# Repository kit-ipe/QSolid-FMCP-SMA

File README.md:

# FMC+ SMA

## Cloning the repository
- Libraries used in the project are in this other [cern repository](https://gitlab.cern.ch/p2-xware/hardware/kicad-pcbs/kit-kicad-library) or [kit repository](https://git.scc.kit.edu/cms-tt/hardware/kicad-pcbs/kit-kicad-library) and need to be linked using an **Environment Variable** inside KiCad (Preferences -> Configure Paths... ->) right after opening the project
 
  `KICAD_USER_LIBRARY = /path/to/KIT_KiCad_Library`

## 3D Views

### Top

### Bottom

## LICENSE

Copyright Luis Ardila, Marvin Fuchs, Robert Gartmann, Lukas Scheller 2023.

This source describes Open Hardware and is licensed under the CERN-OHL-P v2
You may redistribute and modify this documentation and make products
using it under the terms of the CERN-OHL-P v2 [https:/cern.ch/cern-ohl](https:/cern.ch/cern-ohl).
This documentation is distributed WITHOUT ANY EXPRESS OR IMPLIED
WARRANTY, INCLUDING OF MERCHANTABILITY, SATISFACTORY QUALITY
AND FITNESS FOR A PARTICULAR PURPOSE. Please see the CERN-OHL-P v2
for applicable conditions.

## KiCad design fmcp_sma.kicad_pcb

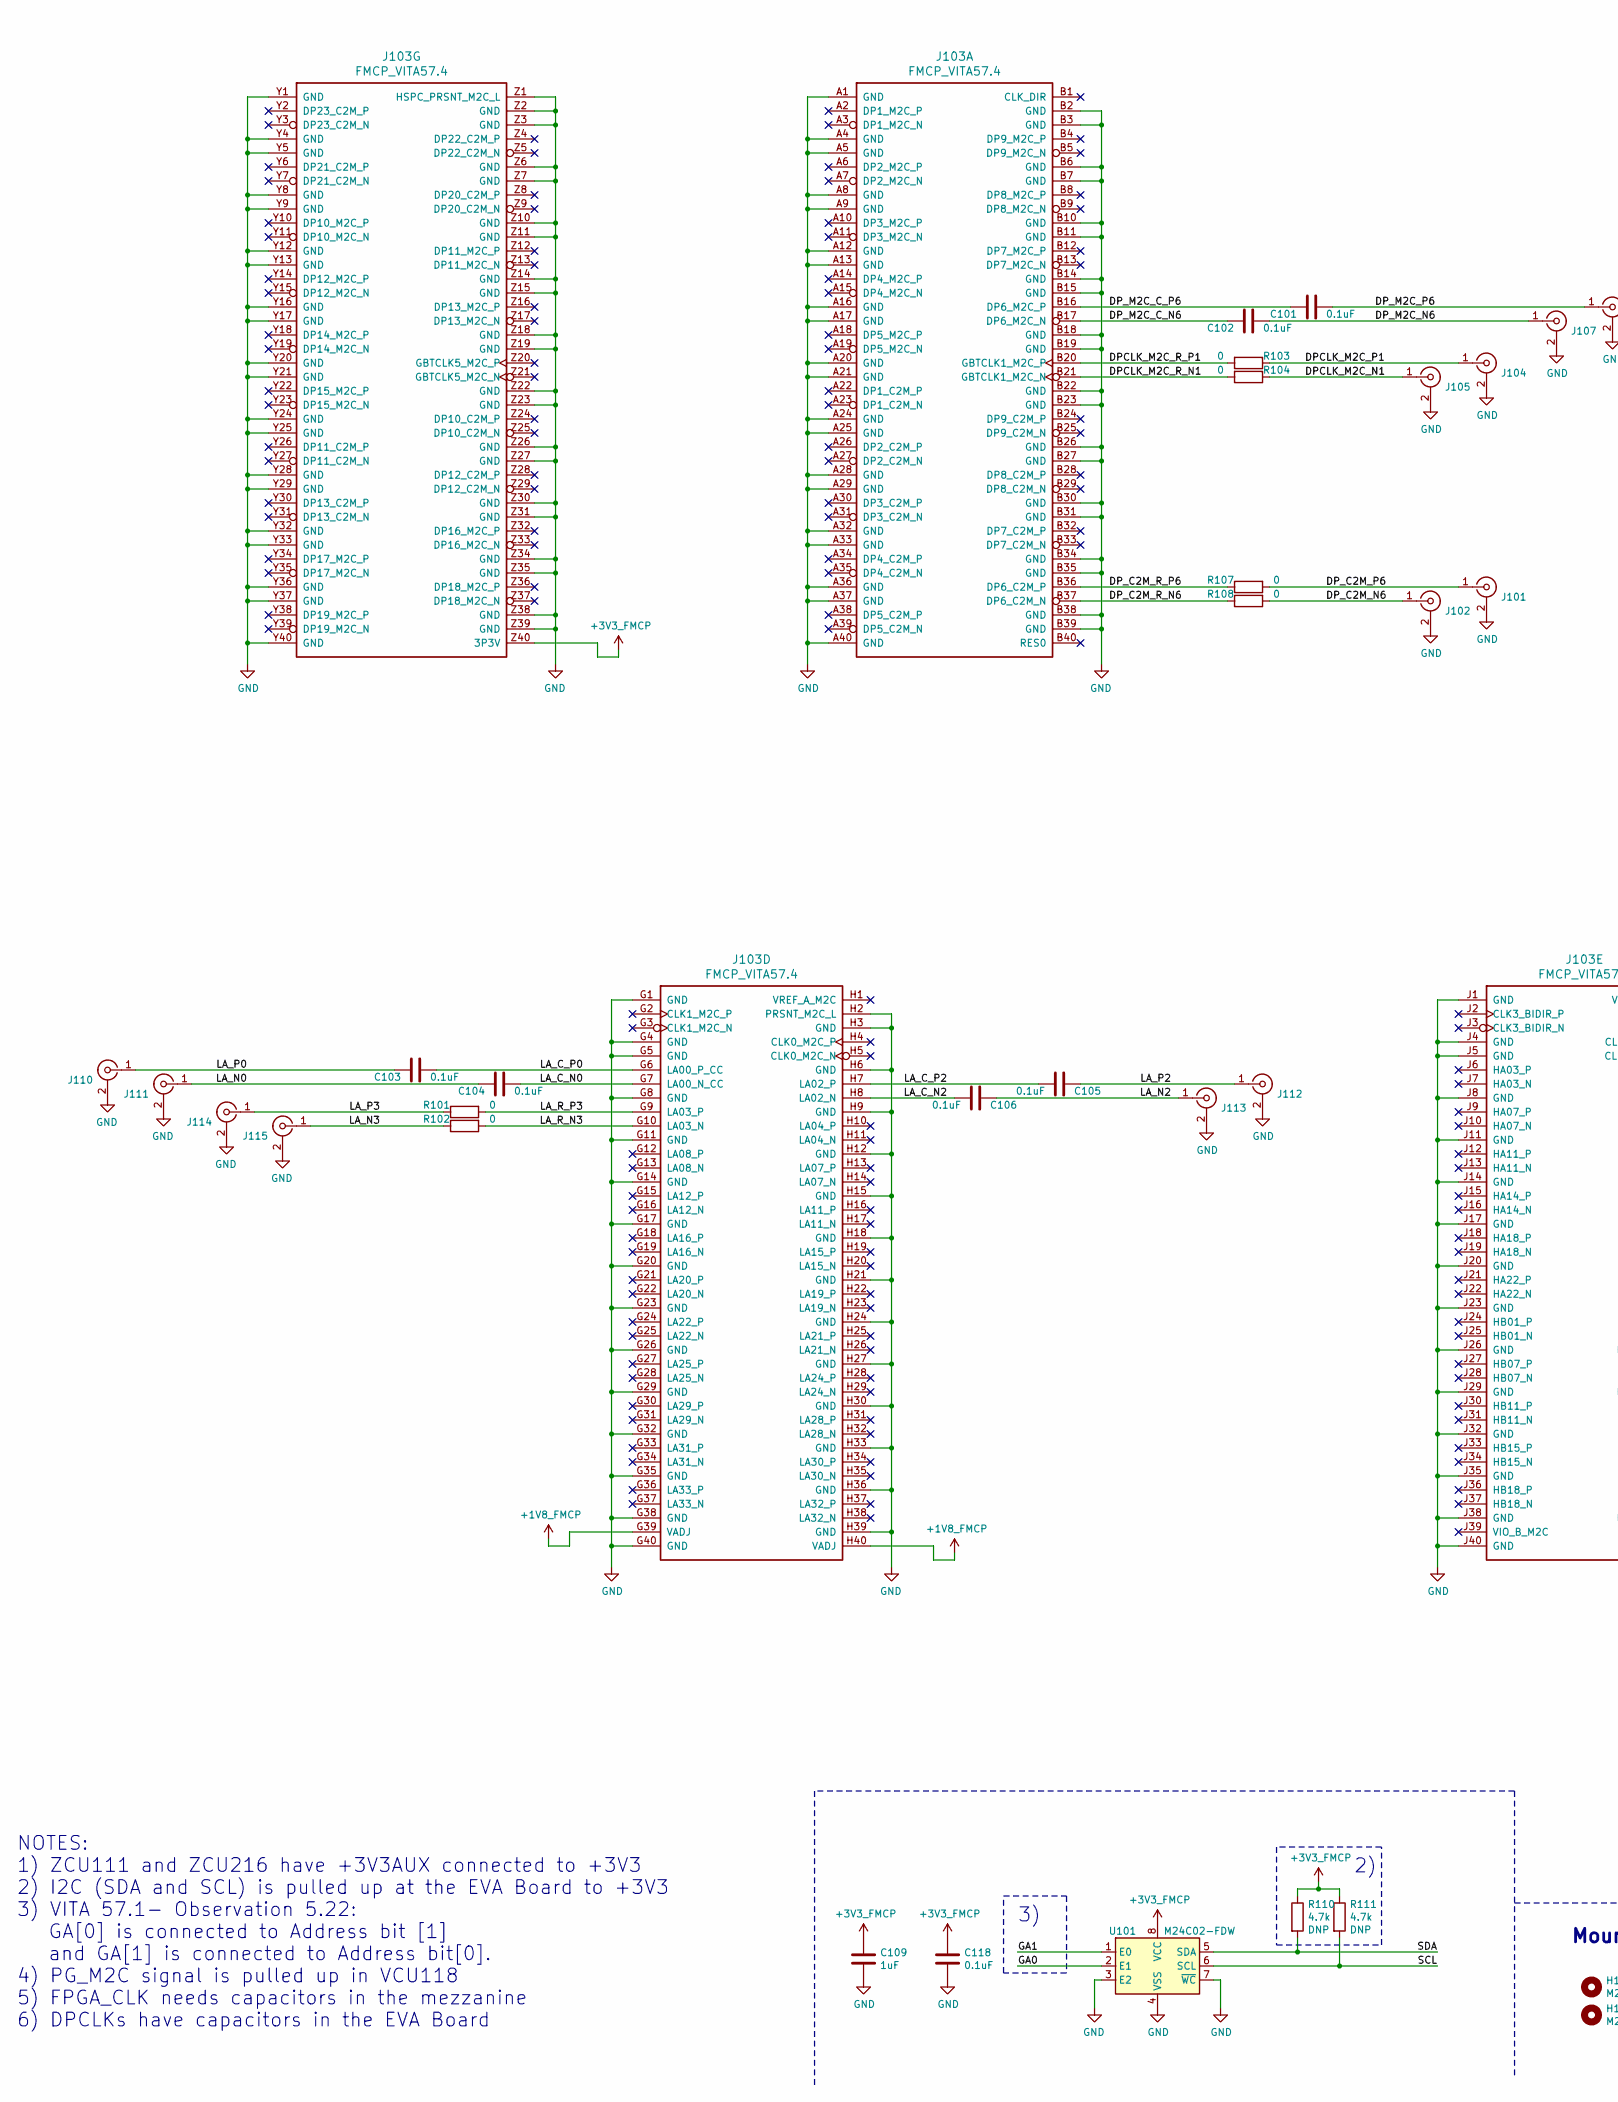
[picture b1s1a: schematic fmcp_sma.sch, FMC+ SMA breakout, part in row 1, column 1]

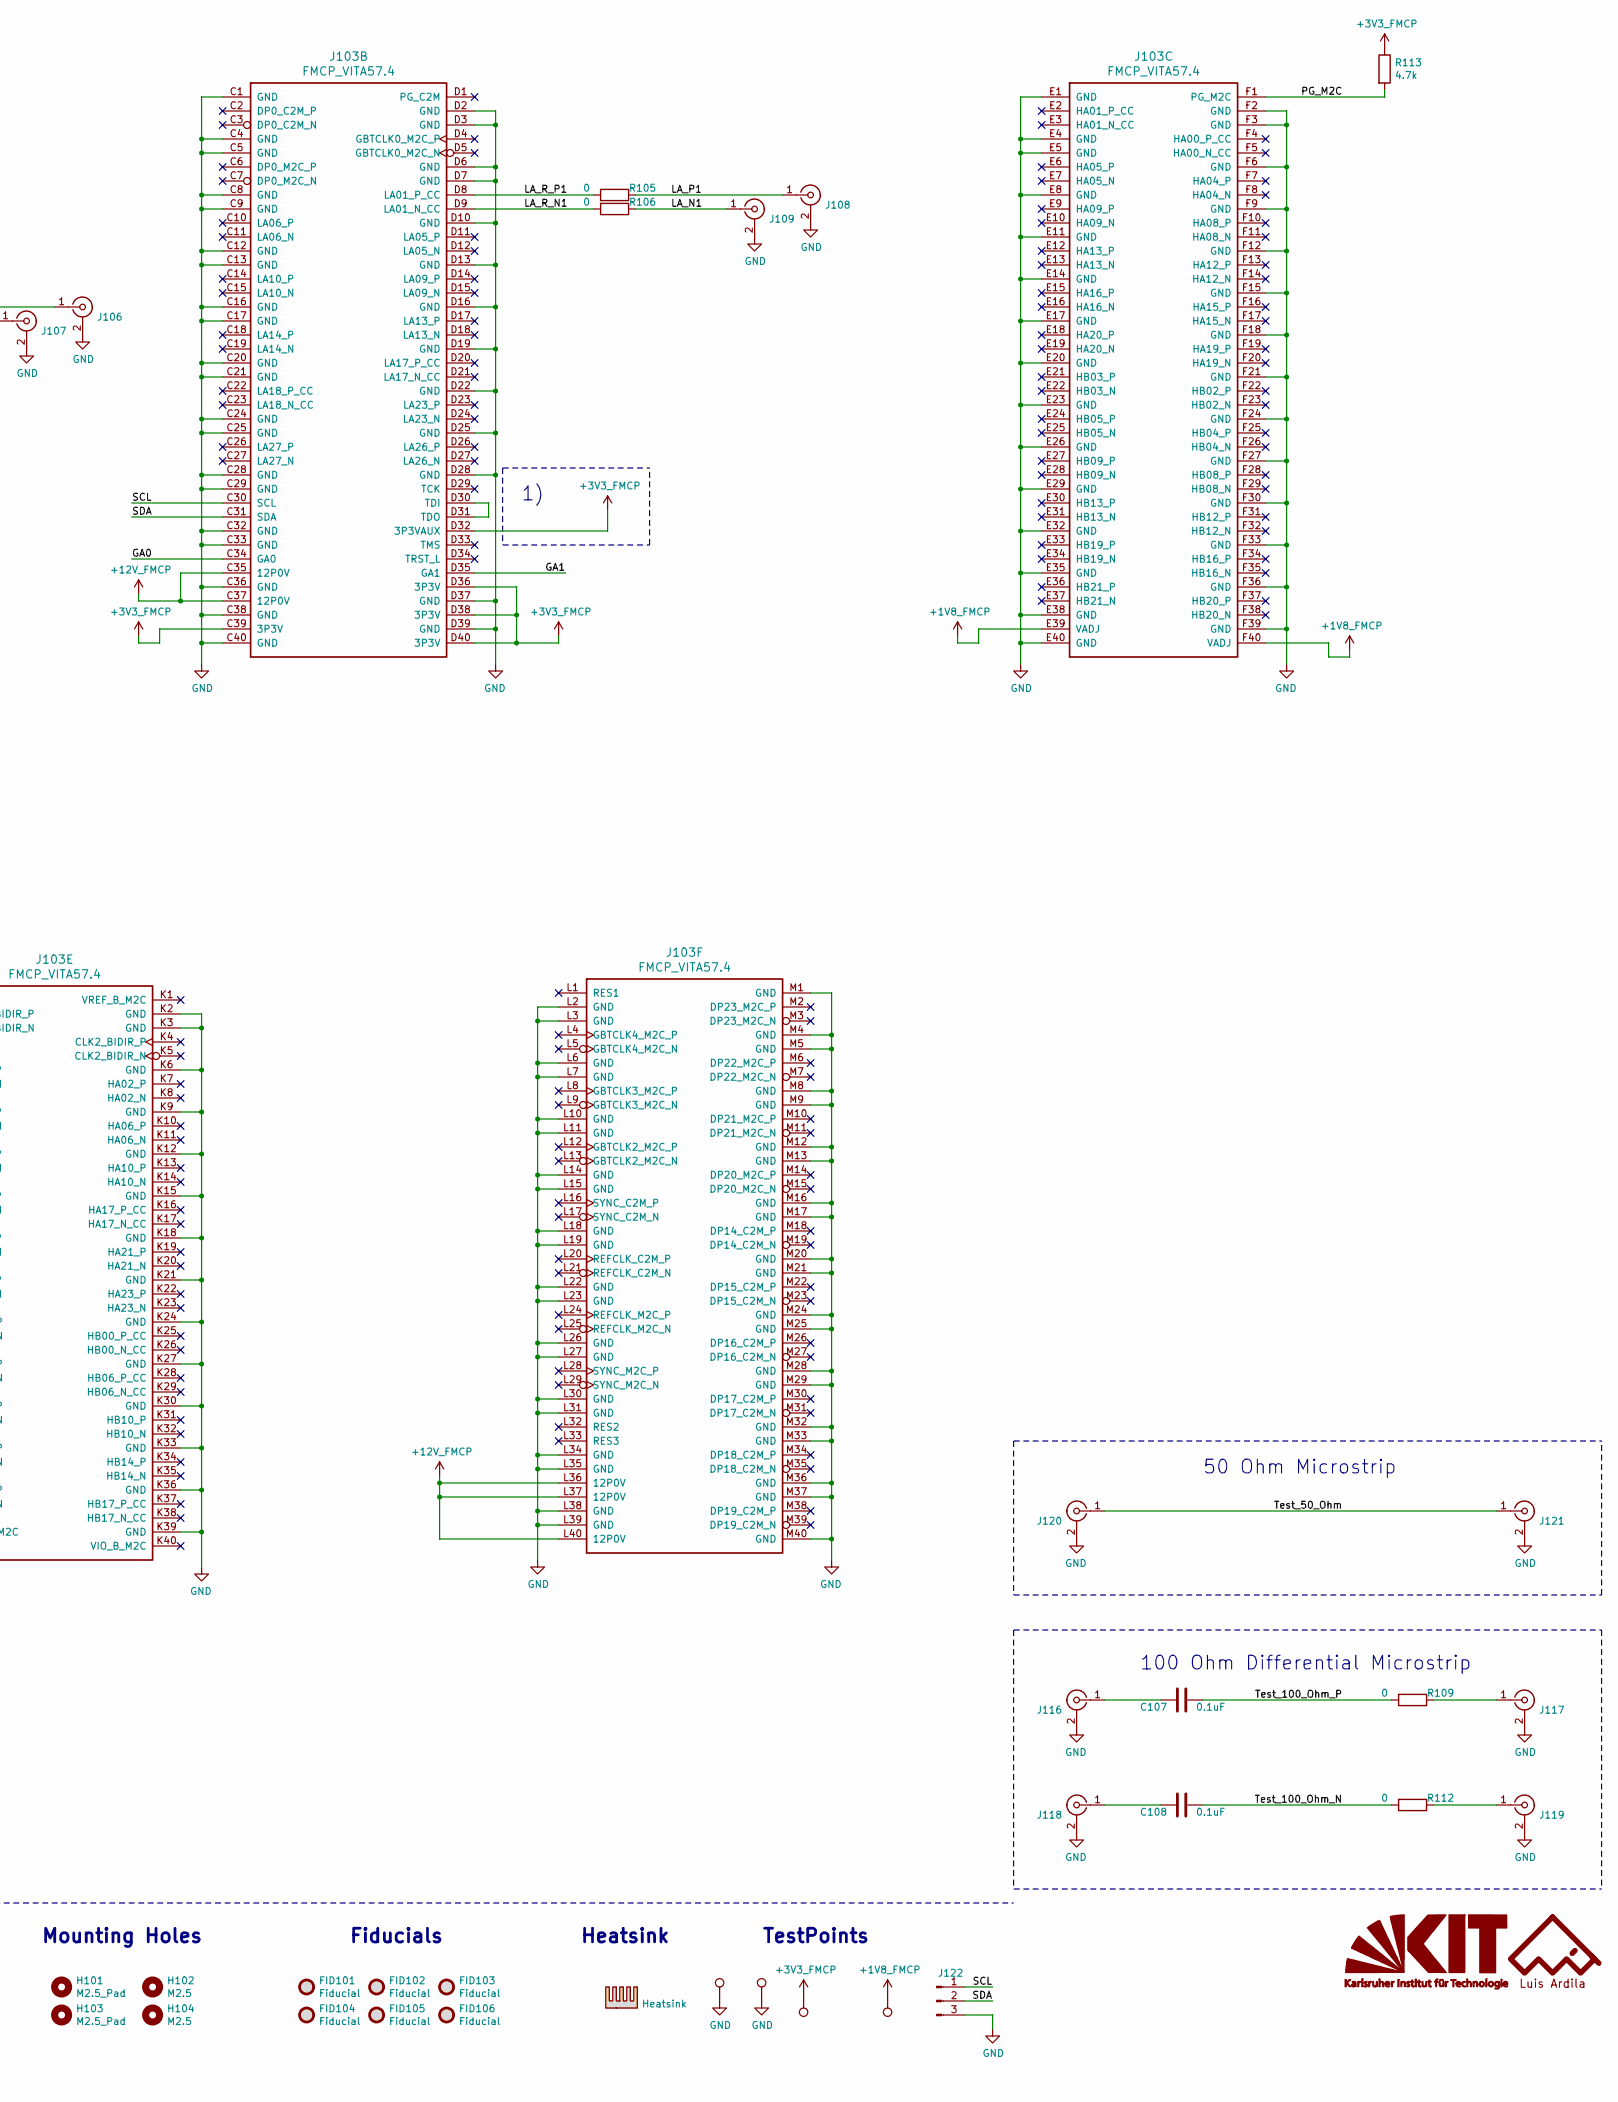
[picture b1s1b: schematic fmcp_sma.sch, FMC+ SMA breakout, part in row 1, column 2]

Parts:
C101, C102, C103, C104, C105, C106, C107, C108: 0.1uF; C_0201_0603Metric
C109: 1uF; C_0603_1608Metric
C118: 0.1uF; C_0603_1608Metric
FID101, FID102, FID103, FID104, FID105, FID106: Fiducial; Fiducial_1mm_Mask2mm
G101: LA_LOGO; LA_LOGO_MASK_NoName
G102: KIT_LOGO; KIT_LOGO_MASK_4.1x1.6mm
H101, H103: M2.5_Pad; MountingHole_2.7mm_M2.5_Pad
H102, H104: M2.5; MountingHole_2.7mm_M2.5
J101, J102, J104, J105, J106, J107, J116, J117, J118, J119, J120, J121: Conn_Coaxial; SF2921-61345-1S
J103: FMCP_VITA57.4; FMC_SEAM_ASP_184330_BGA-560_40x14_55.778x19.76mm
J108, J109, J110, J111, J112, J113, J114, J115: Conn_Coaxial; SMA_Amphenol_132134_Vertical
J122: Conn_01x03_Male; PinHeader_1x03_P2.54mm_Vertical
R101, R102, R103, R104, R105, R106, R107, R108, R109, R112: 0; R_0201_0603Metric
R110, R111: 4.7k; R_0603_1608Metric_DNP
R113: 4.7k; R_0603_1608Metric
TP101, TP102, TP104, TP105: TestPoint; TestPoint_Loop_D2.50mm_Drill1.0mm
U101: M24C02-FDW; TSSOP-8_4.4x3mm_P0.65mm

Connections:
+1V8_FMCP: J103.E39 (VADJ), J103.F40 (VADJ), J103.G39 (VADJ), J103.H40 (VADJ), TP102.1
+3V3_FMCP: C109.1, C118.1, J103.C39 (3P3V), J103.D32 (3P3VAUX), J103.D36 (3P3V), J103.D38 (3P3V), J103.D40 (3P3V), J103.Z40 (3P3V), R110.1, R111.1, R113.1, TP101.1, U101.8 (VCC)
+12V_FMCP: J103.C35 (12P0V), J103.C37 (12P0V), J103.L36 (12P0V), J103.L37 (12P0V), J103.L40 (12P0V)
/DPCLK_M2C_N1: J105.1 (In), R104.1
/DPCLK_M2C_P1: J104.1 (In), R103.1
/DPCLK_M2C_R_N1: J103.B21 (GBTCLK1_M2C_N), R104.2
/DPCLK_M2C_R_P1: J103.B20 (GBTCLK1_M2C_P), R103.2
/DP_C2M_N6: J102.1 (In), R108.2
/DP_C2M_P6: J101.1 (In), R107.2
/DP_C2M_R_N6: J103.B37 (DP6_C2M_N), R108.1
/DP_C2M_R_P6: J103.B36 (DP6_C2M_P), R107.1
/DP_M2C_C_N6: C102.1, J103.B17 (DP6_M2C_N)
/DP_M2C_C_P6: C101.1, J103.B16 (DP6_M2C_P)
/DP_M2C_N6: C102.2, J107.1 (In)
/DP_M2C_P6: C101.2, J106.1 (In)
/GA0: J103.C34 (GA0), U101.2 (E1)
/GA1: J103.D35 (GA1), U101.1 (E0)
/LA_C_N0: C104.2, J103.G7 (LA00_N_CC)
/LA_C_N2: C106.2, J103.H8 (LA02_N)
/LA_C_P0: C103.2, J103.G6 (LA00_P_CC)
/LA_C_P2: C105.2, J103.H7 (LA02_P)
/LA_N0: C104.1, J111.1 (In)
/LA_N1: J109.1 (In), R106.1
/LA_N2: C106.1, J113.1 (In)
/LA_N3: J115.1 (In), R102.1
/LA_P0: C103.1, J110.1 (In)
/LA_P1: J108.1 (In), R105.1
/LA_P2: C105.1, J112.1 (In)
/LA_P3: J114.1 (In), R101.1
/LA_R_N1: J103.D9 (LA01_N_CC), R106.2
/LA_R_N3: J103.G10 (LA03_N), R102.2
/LA_R_P1: J103.D8 (LA01_P_CC), R105.2
/LA_R_P3: J103.G9 (LA03_P), R101.2
/PG_M2C: J103.F1 (PG_M2C), R113.2
/SCL: J103.C30 (SCL), J122.1, R111.2, U101.6 (SCL)
/SDA: J103.C31 (SDA), J122.2, R110.2, U101.5 (SDA)
/Test_50_Ohm: J120.1 (In), J121.1 (In)
/Test_100_Ohm_N: C108.2, R112.2
/Test_100_Ohm_P: C107.2, R109.2
GND: C109.2, C118.2, J101.2 (Ext), J102.2 (Ext), J103.A1 (GND), J103.A4 (GND), J103.A5 (GND), J103.A8 (GND), J103.A9 (GND), J103.A12 (GND), J103.A13 (GND), J103.A16 (GND), J103.A17 (GND), J103.A20 (GND), J103.A21 (GND), J103.A24 (GND), J103.A25 (GND), J103.A28 (GND), J103.A29 (GND), J103.A32 (GND), J103.A33 (GND), J103.A36 (GND), J103.A37 (GND), J103.A40 (GND), J103.B2 (GND), J103.B3 (GND), J103.B6 (GND), J103.B7 (GND), J103.B10 (GND), J103.B11 (GND), J103.B14 (GND), J103.B15 (GND), J103.B18 (GND), J103.B19 (GND), J103.B22 (GND), J103.B23 (GND), J103.B26 (GND), J103.B27 (GND), J103.B30 (GND), J103.B31 (GND), J103.B34 (GND), J103.B35 (GND), J103.B38 (GND), J103.B39 (GND), J103.C1 (GND), J103.C4 (GND), J103.C5 (GND), J103.C8 (GND), J103.C9 (GND), J103.C12 (GND), J103.C13 (GND), J103.C16 (GND), J103.C17 (GND), J103.C20 (GND), J103.C21 (GND), J103.C24 (GND), J103.C25 (GND), J103.C28 (GND), J103.C29 (GND), J103.C32 (GND), J103.C33 (GND), J103.C36 (GND), J103.C38 (GND), J103.C40 (GND), J103.D2 (GND), J103.D3 (GND), J103.D6 (GND), J103.D7 (GND), J103.D10 (GND), J103.D13 (GND), J103.D16 (GND), J103.D19 (GND), J103.D22 (GND), J103.D25 (GND), J103.D28 (GND), J103.D37 (GND), J103.D39 (GND), J103.E1 (GND), J103.E4 (GND), J103.E5 (GND), J103.E8 (GND), J103.E11 (GND), J103.E14 (GND), J103.E17 (GND), J103.E20 (GND), J103.E23 (GND), J103.E26 (GND), J103.E29 (GND), J103.E32 (GND), J103.E35 (GND), J103.E38 (GND), J103.E40 (GND), J103.F2 (GND), J103.F3 (GND), J103.F6 (GND), J103.F9 (GND), J103.F12 (GND), J103.F15 (GND), J103.F18 (GND), J103.F21 (GND), J103.F24 (GND), J103.F27 (GND), J103.F30 (GND), J103.F33 (GND), J103.F36 (GND), J103.F39 (GND), J103.G1 (GND), J103.G4 (GND), J103.G5 (GND), J103.G8 (GND), J103.G11 (GND), J103.G14 (GND), J103.G17 (GND), J103.G20 (GND), J103.G23 (GND), J103.G26 (GND), J103.G29 (GND), J103.G32 (GND), J103.G35 (GND), J103.G38 (GND), J103.G40 (GND), J103.H2 (PRSNT_M2C_L), J103.H3 (GND), J103.H6 (GND), J103.H9 (GND), J103.H12 (GND), J103.H15 (GND), J103.H18 (GND), J103.H21 (GND), J103.H24 (GND), J103.H27 (GND), J103.H30 (GND), J103.H33 (GND), J103.H36 (GND), J103.H39 (GND), J103.J1 (GND), J103.J4 (GND), J103.J5 (GND), J103.J8 (GND), J103.J11 (GND), J103.J14 (GND), J103.J17 (GND), J103.J20 (GND), J103.J23 (GND), J103.J26 (GND), J103.J29 (GND), J103.J32 (GND), J103.J35 (GND), J103.J38 (GND), J103.J40 (GND), J103.K2 (GND), J103.K3 (GND), J103.K6 (GND), J103.K9 (GND), J103.K12 (GND), J103.K15 (GND), J103.K18 (GND), J103.K21 (GND), J103.K24 (GND), J103.K27 (GND), J103.K30 (GND), J103.K33 (GND), J103.K36 (GND), J103.K39 (GND), J103.L2 (GND), J103.L3 (GND), J103.L6 (GND), J103.L7 (GND), J103.L10 (GND), J103.L11 (GND), J103.L14 (GND), J103.L15 (GND), J103.L18 (GND), J103.L19 (GND), J103.L22 (GND), J103.L23 (GND), J103.L26 (GND), J103.L27 (GND), J103.L30 (GND), J103.L31 (GND), J103.L34 (GND), J103.L35 (GND), J103.L38 (GND), J103.L39 (GND), J103.M1 (GND), J103.M4 (GND), J103.M5 (GND), J103.M8 (GND), J103.M9 (GND), J103.M12 (GND), J103.M13 (GND), J103.M16 (GND), J103.M17 (GND), J103.M20 (GND), J103.M21 (GND), J103.M24 (GND), J103.M25 (GND), J103.M28 (GND), J103.M29 (GND), J103.M32 (GND), J103.M33 (GND), J103.M36 (GND), J103.M37 (GND), J103.M40 (GND), J103.Y1 (GND), J103.Y4 (GND), J103.Y5 (GND), J103.Y8 (GND), J103.Y9 (GND), J103.Y12 (GND), J103.Y13 (GND), J103.Y16 (GND), J103.Y17 (GND), J103.Y20 (GND), J103.Y21 (GND), J103.Y24 (GND), J103.Y25 (GND), J103.Y28 (GND), J103.Y29 (GND), J103.Y32 (GND), J103.Y33 (GND), J103.Y36 (GND), J103.Y37 (GND), J103.Y40 (GND), J103.Z1 (HSPC_PRSNT_M2C_L), J103.Z2 (GND), J103.Z3 (GND), J103.Z6 (GND), J103.Z7 (GND), J103.Z10 (GND), J103.Z11 (GND), J103.Z14 (GND), J103.Z15 (GND), J103.Z18 (GND), J103.Z19 (GND), J103.Z22 (GND), J103.Z23 (GND), J103.Z26 (GND), J103.Z27 (GND), J103.Z30 (GND), J103.Z31 (GND), J103.Z34 (GND), J103.Z35 (GND), J103.Z38 (GND), J103.Z39 (GND), J104.2 (Ext), J105.2 (Ext), J106.2 (Ext), J107.2 (Ext), J108.2 (Ext), J109.2 (Ext), J110.2 (Ext), J111.2 (Ext), J112.2 (Ext), J113.2 (Ext), J114.2 (Ext), J115.2 (Ext), J116.2 (Ext), J117.2 (Ext), J118.2 (Ext), J119.2 (Ext), J120.2 (Ext), J121.2 (Ext), J122.3, TP104.1, TP105.1, U101.3 (E2), U101.4 (VSS), U101.7 (~WC)
unnamed: C107.1, J116.1 (In)
unnamed: C108.1, J118.1 (In)
unnamed: J103.D30 (TDI), J103.D31 (TDO)
unnamed: J117.1 (In), R109.1
unnamed: J119.1 (In), R112.1

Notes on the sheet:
Mounting Holes
Fiducials
Heatsink
TestPoints
NOTES: 1) ZCU111 and ZCU216 have +3V3AUX connected to +3V3 2) I2C (SDA and SCL) is pulled up at the EVA Board to +3V3 3) VITA 57.1- Observation 5.22: GA[0] is connected to Address bit [1] and GA[1] is connected to Address bit[0]. 4) PG_M2C signal is pulled up in VCU118 5) FPGA_CLK needs capacitors 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
100 Ohm Differential Microstrip
50 Ohm Microstrip

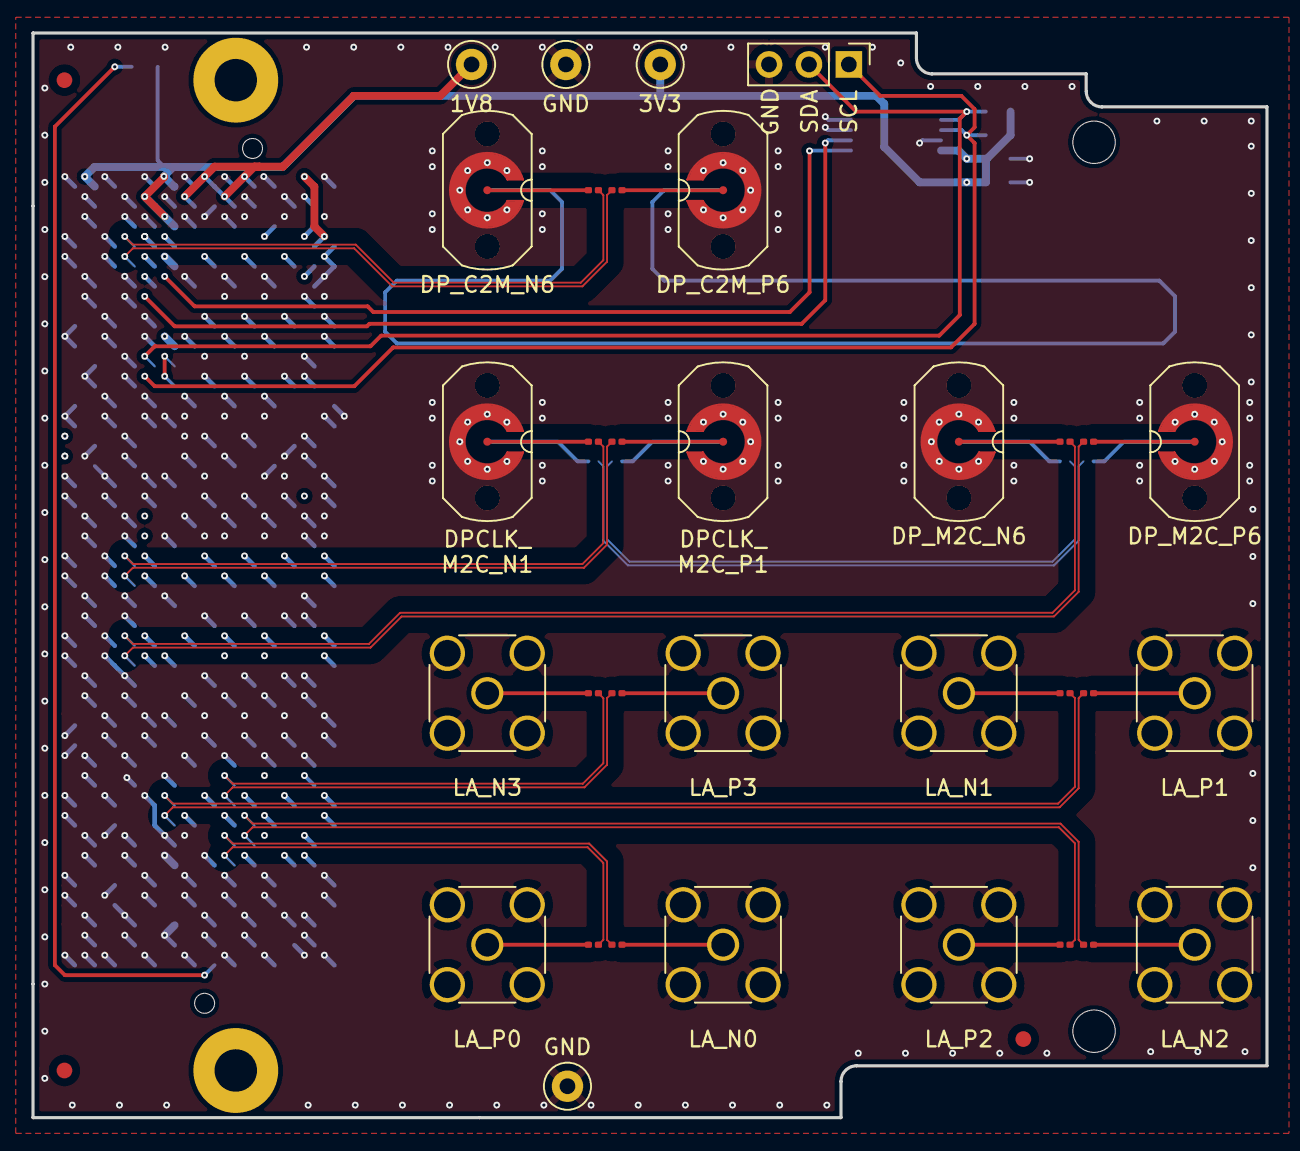
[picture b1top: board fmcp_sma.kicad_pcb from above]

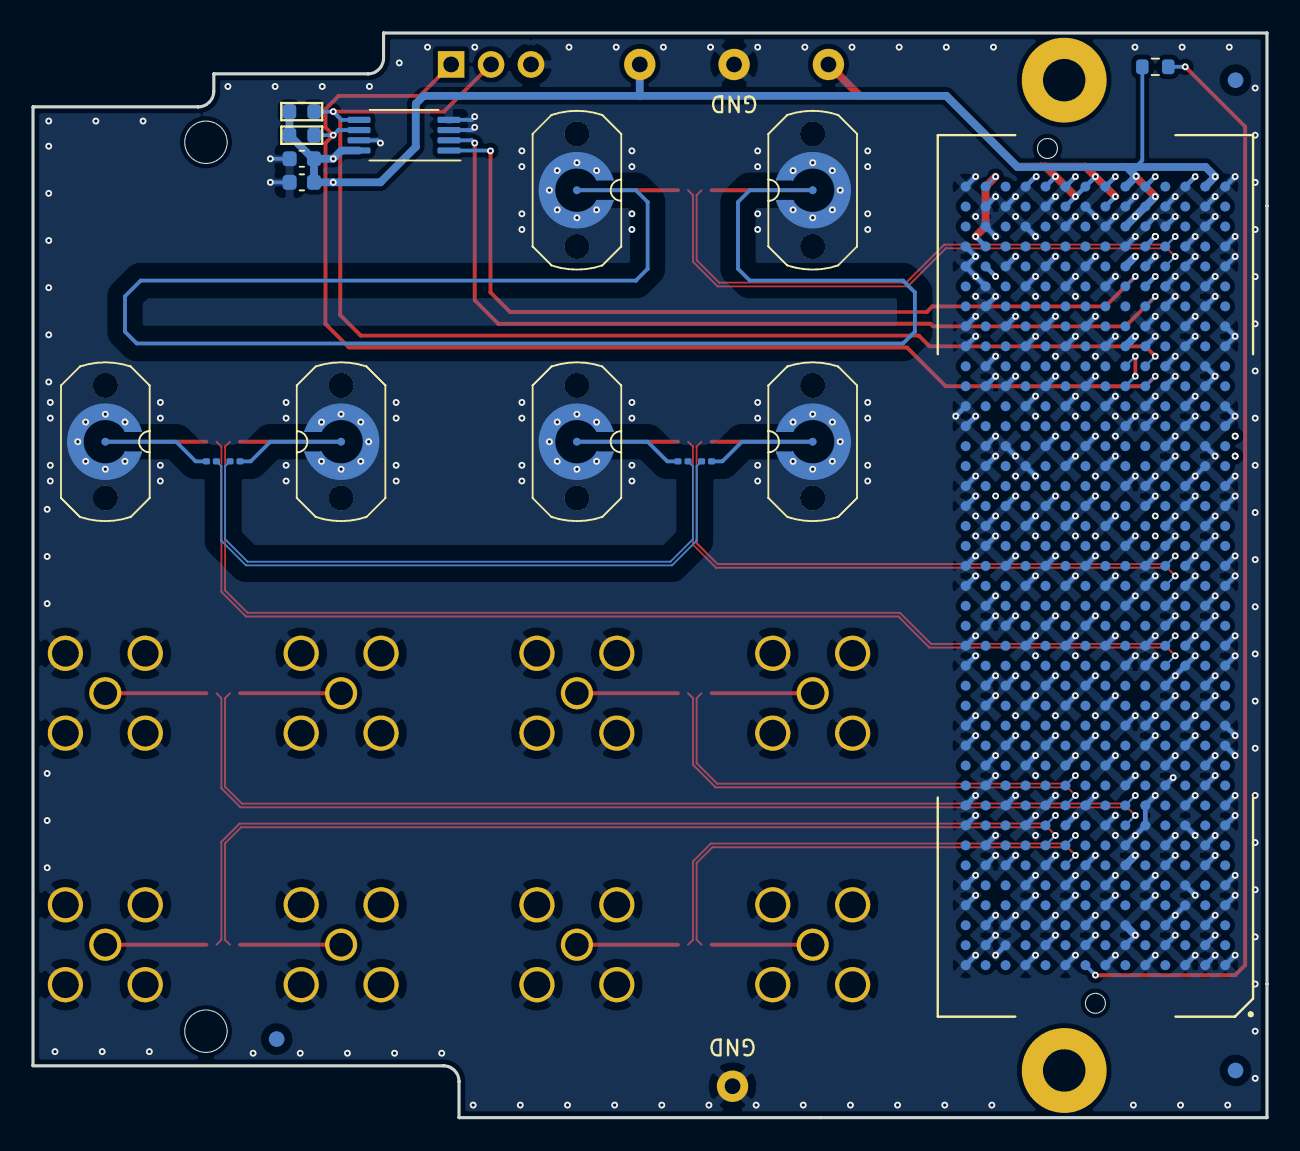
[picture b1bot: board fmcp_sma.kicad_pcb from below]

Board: 4 copper layers, 78.5 x 69.0 mm, 63 parts (20 on the bottom side), 45 nets.

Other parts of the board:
Board_Stackup-4Layer: Board_Stackup-4Layer; Board_Stackup-4Layer-Metric

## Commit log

2022-12-01 adding smas
2022-12-01 added pdf
2022-12-01 images
2022-12-01 update block diagram
2022-12-06 updated footprint
2022-12-07 routed
2022-12-07 gerbers
2022-12-09 modified footprint for screw on sma conn@
2022-12-09 re-pour zones with 0.3 clearance and 1mm for traces only
2022-12-12 updated gerbers
2022-12-13 as fabricated
2022-12-21 bom csv xml
2023-01-03 update stackup
2023-01-03 add license

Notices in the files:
fmcp_sma.kicad_pcb:
Licensed under CERN-OHL-P v2
